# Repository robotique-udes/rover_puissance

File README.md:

# rover_puissance
Répertoire de l'équipe de puissance

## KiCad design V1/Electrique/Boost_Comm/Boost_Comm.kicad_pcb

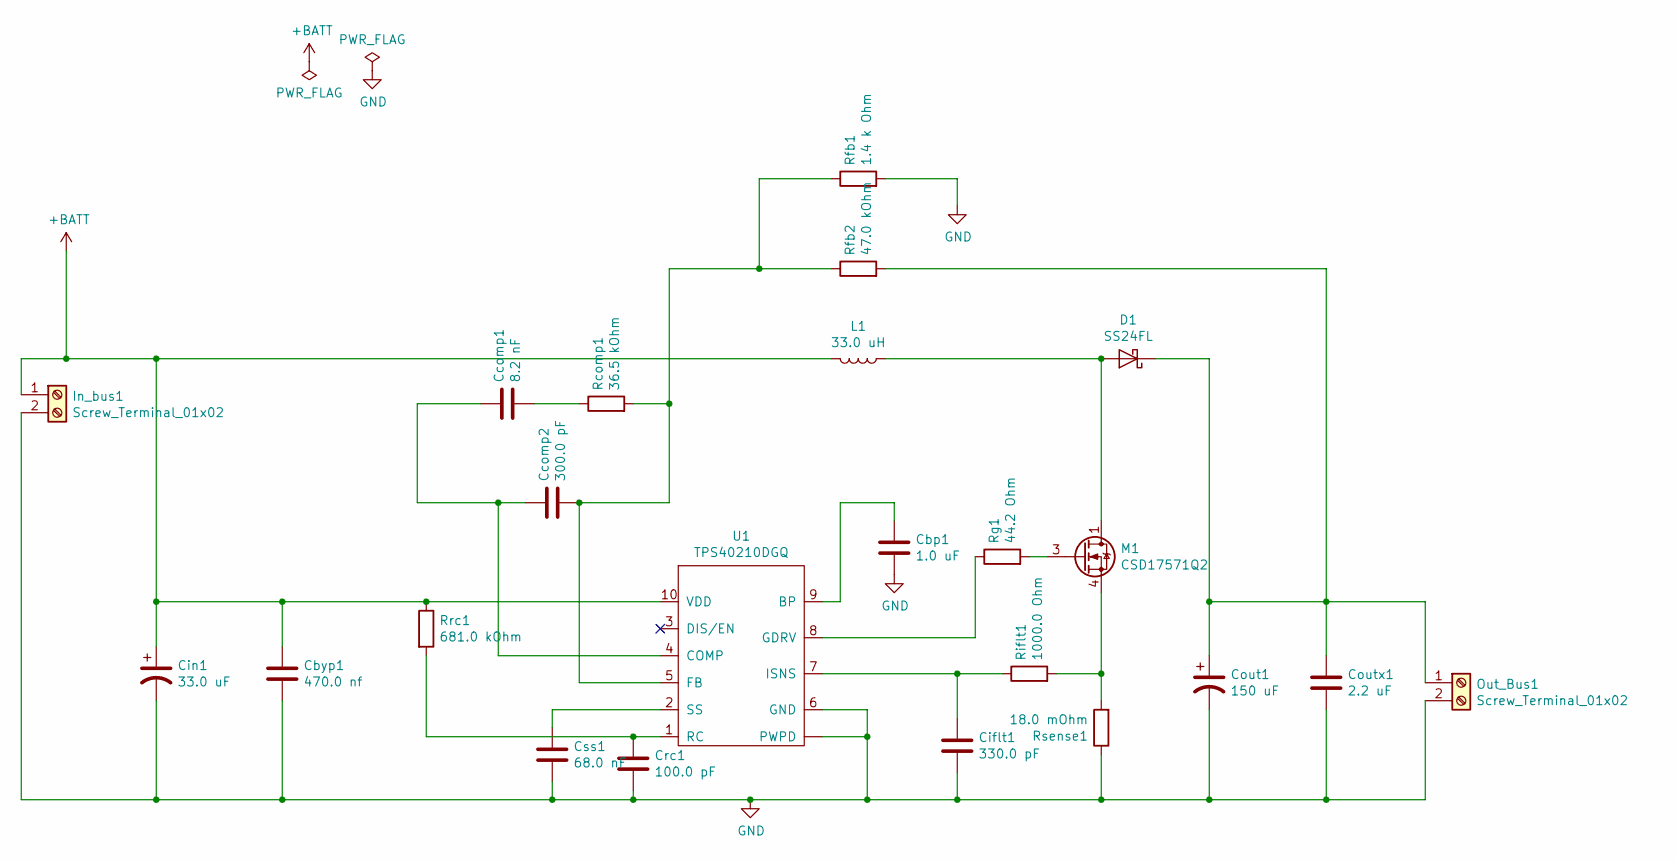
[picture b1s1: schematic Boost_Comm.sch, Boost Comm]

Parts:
Cbp1: 1.0 uF; C_0805_2012Metric
Cbyp1: 470.0 nf; C_0805_2012Metric
Ccomp1: 8.2 nF; C_0805_2012Metric
Ccomp2: 300.0 pF; C_0805_2012Metric
Ciflt1: 330.0 pF; C_0805_2012Metric
Cin1: 33.0 uF; CAP_EEE-FT1H470AP
Cout1: 150 uF; CAP_EEHZA1V151P
Coutx1: 2.2 uF; C_1206_3216Metric
Crc1: 100.0 pF; C_1206_3216Metric
Css1: 68.0 nF; C_0402_1005Metric
D1: SS24FL; D_SOD-123F
In_bus1: Screw_Terminal_01x02; TerminalBlock_bornier-2_P5.08mm
L1: 33.0 uH; L_Wuerth_HCI-1365
M1: CSD17571Q2; 7inch_SON_2x2_mm
Out_Bus1: Screw_Terminal_01x02; TerminalBlock_bornier-2_P5.08mm
Rcomp1: 36.5 kOhm; R_0201_0603Metric
Rfb1: 1.4 k Ohm; R_0402_1005Metric
Rfb2: 47.0 kOhm; R_0603_1608Metric_Pad1.05x0.95mm_HandSolder
Rg1: 44.2 Ohm; R_0402_1005Metric
Riflt1: 1000.0 Ohm; R_0402_1005Metric
Rrc1: 681.0 kOhm; R_0201_0603Metric
Rsense1: 18.0 mOhm; R_0612_1632Metric_Pad1.18x3.40mm_HandSolder
U1: TPS40210DGQ; TSSOP-10_3x3mm_P0.5mm_ThermalPad

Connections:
+BATT: Cbyp1.1, Cin1.1, In_bus1.1, L1.2, Rrc1.1, U1.10 (VDD)
GND: Cbp1.2, Cbyp1.2, Ciflt1.2, Cin1.2, Cout1.2, Coutx1.2, Crc1.2, Css1.2, In_bus1.2, Out_Bus1.2, Rfb1.2, Rsense1.1, U1.6 (GND), U1.~ (PWPD)
unnamed: Cbp1.1, U1.9 (BP)
unnamed: Ccomp1.1, Ccomp2.1, U1.4 (COMP)
unnamed: Ccomp1.2, Rcomp1.1
unnamed: Ccomp2.2, Rcomp1.2, Rfb1.1, Rfb2.1, U1.5 (FB)
unnamed: Ciflt1.1, Riflt1.1, U1.7 (ISNS)
unnamed: Cout1.1, Coutx1.1, D1.1 (K), Out_Bus1.1, Rfb2.2
unnamed: Crc1.1, Rrc1.2, U1.1 (RC)
unnamed: Css1.1, U1.2 (SS)
unnamed: D1.2 (A), L1.1, M1.1 (D)
unnamed: M1.3 (G), Rg1.2
unnamed: M1.4 (S), Riflt1.2, Rsense1.2
unnamed: Rg1.1, U1.8 (GDRV)

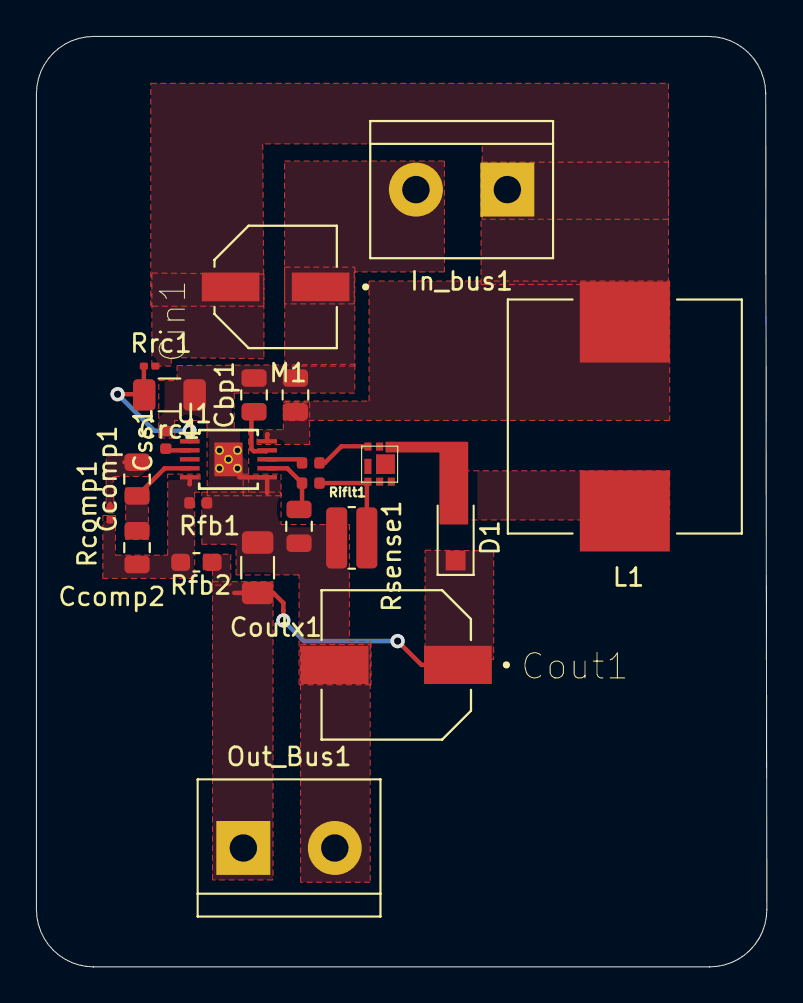
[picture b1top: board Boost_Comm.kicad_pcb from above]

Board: 2 copper layers, 40.6 x 51.7 mm, 23 parts (0 on the bottom side), 14 nets.

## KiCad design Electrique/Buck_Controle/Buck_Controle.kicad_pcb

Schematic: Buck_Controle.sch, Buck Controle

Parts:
Cboot1: 10nF; C_0805_2012Metric
Cin1, Cin2, Cin3: 10uF; C_0805_2012Metric
Cout1: 330uF; CAP_TANT_2917
D1: SBRD10200TR; D_SMC
L1: 15uH; L_Bourns_SRR1210A
Rfbb1: 3.24k; R_0805_2012Metric
Rfbt1: 10k; R_0805_2012Metric
U1: TPS5450DDA; TI_SO-PowerPAD-8_ThermalVias
in_bus1: Screw_Terminal_01x02; TerminalBlock_bornier-2_P5.08mm
out_bus1: Screw_Terminal_01x02; TerminalBlock_bornier-2_P5.08mm

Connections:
+BATT: Cin1.1, Cin2.1, Cin3.1, U1.7 (VIN), in_bus1.1
/Vout: Cout1.1, L1.1, Rfbt1.1, out_bus1.1
GND: Cin1.2, Cin2.2, Cin3.2, Cout1.2, D1.2 (A), Rfbb1.2, U1.6 (GND), U1.9 (PW_PAD), in_bus1.2, out_bus1.2
unnamed: Cboot1.1, D1.1 (K), L1.2, U1.8 (PH)
unnamed: Cboot1.2, U1.1 (BOOT)
unnamed: Rfbb1.1, Rfbt1.2, U1.4 (VSENSE)

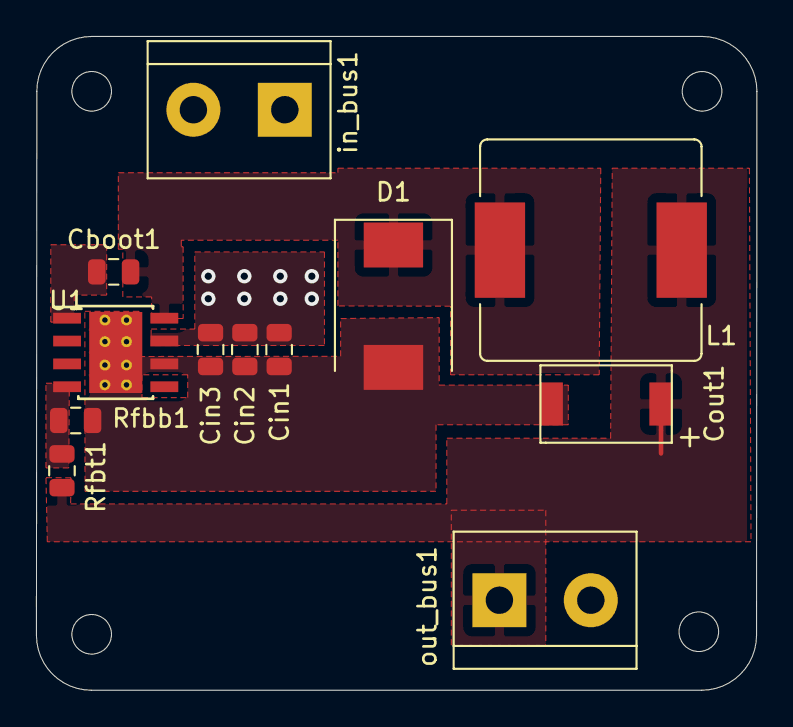
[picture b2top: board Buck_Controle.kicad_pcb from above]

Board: 2 copper layers, 40.0 x 36.3 mm, 12 parts (0 on the bottom side), 6 nets.

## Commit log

2020-02-12 Ajout test
2020-02-12 Ajout buck controle
2020-02-12 Formatage du fichier 1
2020-02-12 Ajout design controle
2020-02-12 Ajout cartouche et fichiers de base controle
2020-02-17 footprint - pcb build
2020-02-24 Continuation PCB controle
2020-02-26 Creation du template AUTOCAD
2020-02-26 Update Template
2020-02-26 Updtade i guess
2020-03-02 Schéma boost Comm fini
2020-03-04 Association footprint-composante partielle
2020-03-06 Ajout pieces manquantes Boost
2020-03-18 Placement initiale des pièces sur pcb
2020-04-03 Pcb trace boost update
2020-04-04 Update PCB
2020-04-30 Auto stash before merge of "master" and "origin/master"
2020-06-25 Fix probleme pcb file
2020-07-02 merge_test
2020-07-03 Traces pcb sans MOSFET
2020-07-03 Trace pcb sans MOSFET EP:2
2020-11-16 Changement du footprint comm
    Changement du footprint de m1 dans le convertisseur de communication
2020-11-27 Ajout du bus in/out
    Ajout du bus pour in/out + routage sur la couche du dessous + via pour transférer ces signaux sur les 2 couches
2020-11-29 Changement du branchement de Cboot + DRC pcb controle
2021-01-09 Update du pcb et création du gerbe
2021-01-09 Ajout du repertoire de gestion
    Le répertoire de gestion contient initialement le wbs et le scope definition du V1 du système de puissance
2021-02-20 Schéma bloc V1
2021-02-21 Update git kraken -> github
2021-02-22 Ajoute des critères des activités de l'électroniques
2021-02-23 Création de l'application BOMCreator
    added gitignore
2021-02-24 Ajustement schéma bloc V1
2021-02-27 Réarragnement des folders dans le git
2021-02-27 Correction folder supplémentaire dans le repos GITHUB
2021-02-28 Ajout du schéma de séquences des activités + ajustement du repos
2021-02-28 correction écriture schéma séquence
2021-02-28 Fix schéma de séquence
    Ajout de la dépendance entre les fixation et l'électronique
2021-03-30 Schéma-bloc V2
2021-06-03 Ca fait longtemps que ya des trucs de pas pusher
2021-06-04 envoi drawio
2021-06-06 Update schéma électrique
2021-06-08 Ajout ventilation
    Schéma draw.io + PNG
    Excel avec recherche/BOM
    À vérifier
2021-06-09 Battery module + Proportion diagrams
2021-06-14 Push pour le review 1
2021-06-16 Mise à jour schéma et ffolder de specsheets
    -Ajout des specsheets
    -ajout des drives dans les specsheet
    -mise a ajout des moteurs dans les specsheets
    -Ajout des encodeur dans les specsheets
    -Mise a jour de moteur du bras dans le schéma
    -ajout des drive du bras dans le schéma(Excepté celle du servo)
